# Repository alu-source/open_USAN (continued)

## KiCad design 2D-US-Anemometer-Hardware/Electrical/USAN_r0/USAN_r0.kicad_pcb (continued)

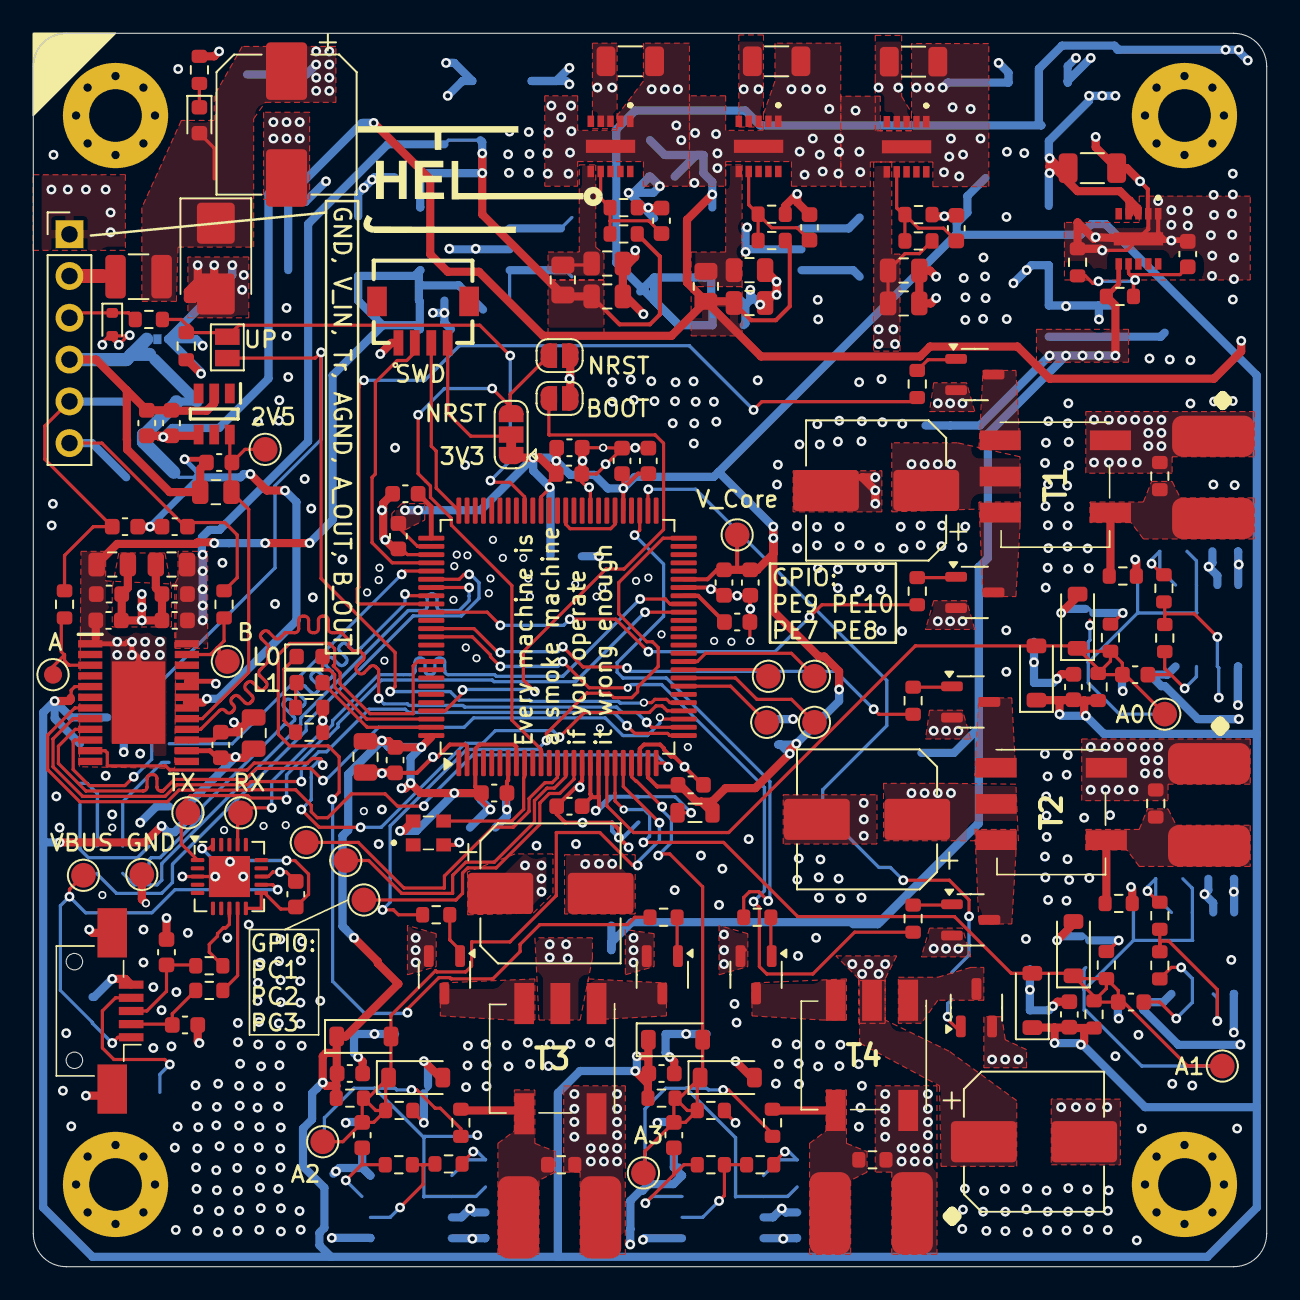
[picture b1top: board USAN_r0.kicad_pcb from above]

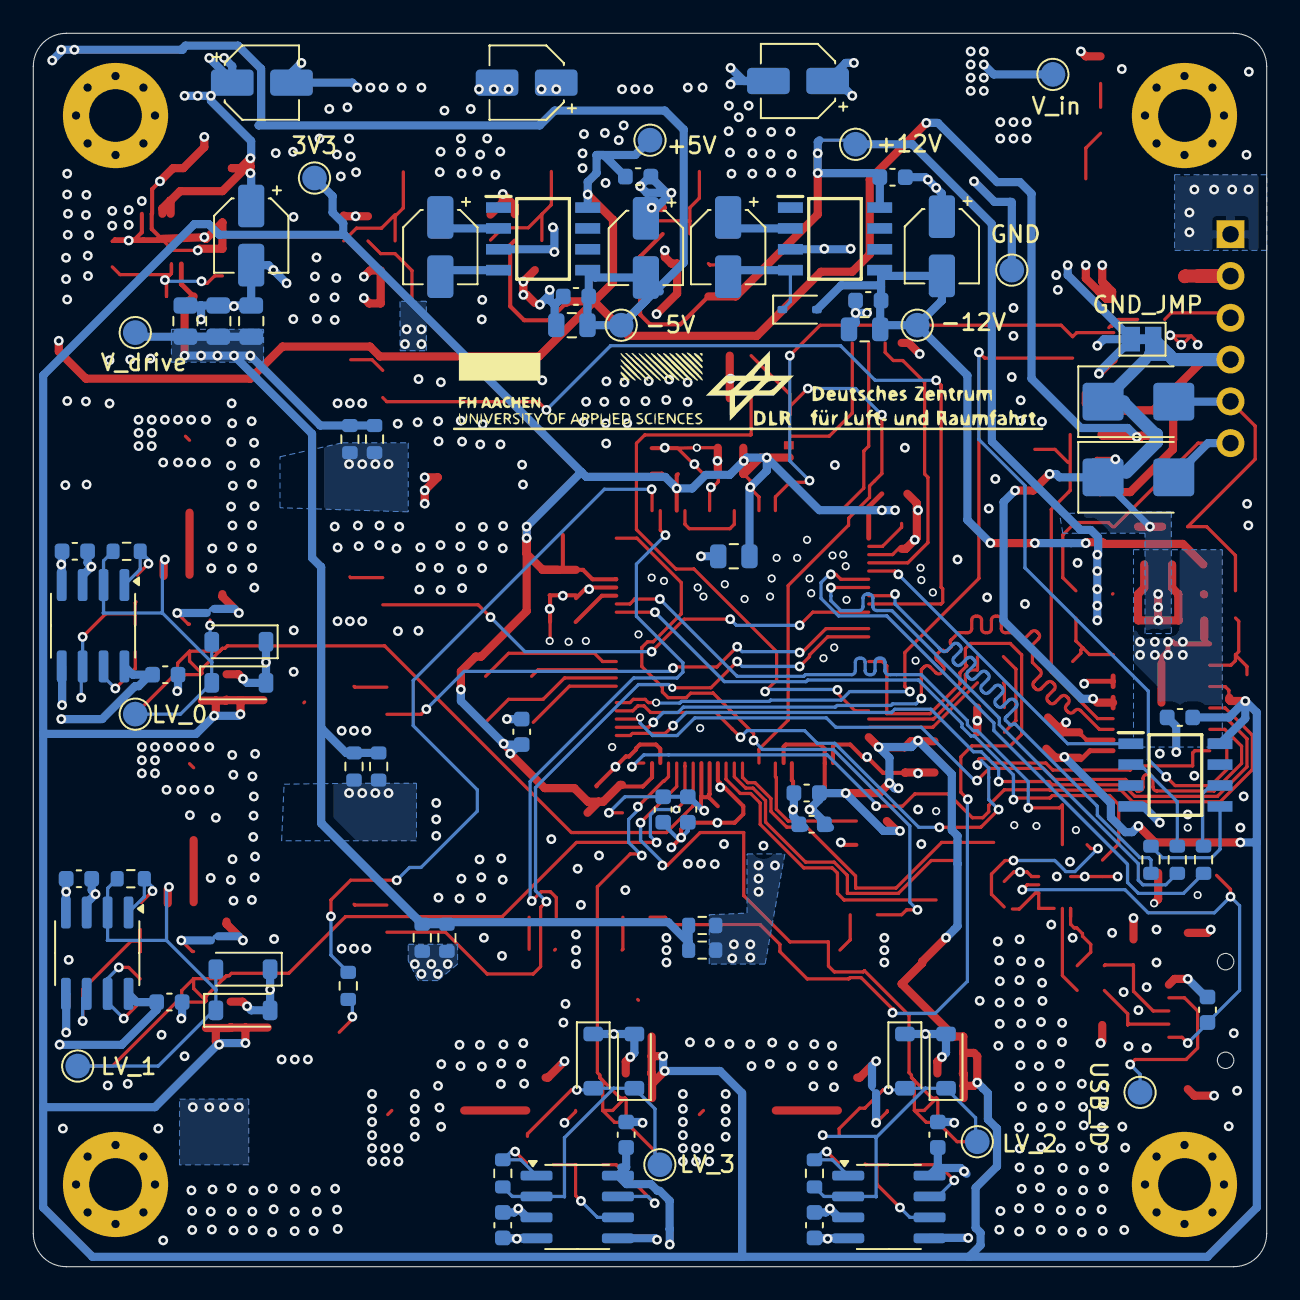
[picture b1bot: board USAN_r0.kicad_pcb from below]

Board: 4 copper layers, 75.0 x 75.0 mm, 259 parts (81 on the bottom side), 123 nets.

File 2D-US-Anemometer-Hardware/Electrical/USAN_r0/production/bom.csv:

Designator,Footprint,Quantity,Value,LCSC Part #
"C1, C28, C6, C67",0805,4,22u,
"C10, C11, C12, C13, C2, C86, C89, C9",CP_Elec_4x5.4,8,"10u, 35V",
C14,CP_Elec_8x10,1,"220uF, 35V",
"C15, C27, C33, C38, C39, C43, C46, C47, C49, C50, C53, C55, C56, C57, C59, C60, C61, C63, C64, C65, C75, C76, C77, C78",0603,24,1u,
"C16, C22, C44, C45, C69, C70, C85",0805,7,4u7,
"C17, C20",0805,2,"4u7, 25V",
"C18, C19, C83, C84",0603,4,"100n, 25V",
"C21, C23, C26, C34, C35, C36, C37, C40, C41, C42, C51, C52, C79, C80, C81",0603,15,100n,
"C29, C30",0603,2,47p,
"C31, C32",0603,2,2u2,
"C4, C82, C88, C92",1206,4,C3216X5R1H106K160AB,
"C48, C54, C58, C62",CP_Elec_8x6.2,4,EEEFK1C221P,
C66,0805,1,DNP (22u),
"C7, C91",0805,2,"10u, 25V",
"C71, C72, C73, C74",0603,4,1u ,
C87,0805,1,10u,
D1,D_SMB,1,    SMBJ24A,
"D10, D11, D12, D13, D14, D15, D16, D17, D18, D19, D4, D5, D6, D7, D8, D9",D_SOD-123,16,BAV20W,
"D2, D20, D3",0603,3,LED Blue,
D21,D_SOD-523,1,ESD5Z5.0T1G,
"D22, D23",D_SMB,2,SMBJ10CA-E3/52,
D25,D_SOD-323,1,BAT54WS-7-F,
F1,1210,1,SMD1210B020TF,
FB1,0805,1,MLZ2012N100LT000 ,
"IC1, IC2",SOIC127P600X175-8N,2,ICL7660ACBAZA,
IC3,SOP65P640X120-25N,1,AD5732AREZ,
IC4,SOT95P280X145-6N,1,REF3425TIDBVR,
IC5,SOIC127P600X175-8N,1,DNP (IS66WVS4M8BLL-104NLI-TR),
"ID1, T_-12V1, T_-5V1, T_12V1, T_24V1, T_3V3, T_5V1, T_Analog1, T_Analog2, T_Analog3, T_Analog4, T_DAC_A1, T_DAC_B1, T_GND1, T_GND2, T_GND3, T_GND4, T_GND5, T_PC1, T_PC2, T_PC3, T_PE10, T_PE7, T_PE8, T_PE9, T_RX1, T_TR_A1, T_TX1, T_VBUS1, T_V_ADJ1, T_V_MCU1, T_V_ref1",TestPoint_Pad_D1.5mm,32,TestPoint,
IN1,PinHeader_1x06_P2.54mm_Vertical,1,DNP (Conn_01x06),
J1,USB_Mini-B_AdamTech_MUSB-B5-S-VT-TSMT-1_SMD_Vertical,1,MUSB-B5-S-VT-TSMT-T/R,
J3,501331-0407,1,501331-0407,
"Q1, Q10, Q11, Q2, Q4, Q5, Q7, Q8",SOT-23-3,8,SI2300DS,
"R1, R19, R20, R29, R30, R43, R44, R57, R58",0603,9,33k,
"R10, R32, R46, R60",0603,4,10k,
"R11, R33, R47, R61",0603,4,1.5k,
"R12, R14, R16, R22, R24, R36, R50, R66",0603,8,47k,
R13,0603,1,20.5k,
"R15, R23, R37, R51",0603,4,6.2k,
"R17, R27, R41, R55",0603,4,100k,
R18,0603,1,11.5k,
R2,0603,1,4k7,
"R21, R26, R35, R4, R40, R49, R54, R9",0603,8,330R,
"R25, R3, R39, R53, R75, R76, R77, R78",0603,8,120R,
R28,0603,1,4.3k,
"R31, R34",0805,2,0R,
"R5, R6",0603,2,27R,
"R68, R69, R7, R70, R71, R8",0603,6,1k,
"R72, R73, R74",0603,3,DNP (27),
"T1, T2, T3, T4",B78416A2232A003,4,B78416A2232A003,
U1,QFN-20-1EP_4x4mm_P0.5mm_EP2.5x2.5mm,1,FT231XQ,
U2,LQFP-100_14x14mm_P0.5mm,1,STM32F469VGTx,
"U3, U4, U5, U6",SOIC-8_3.9x4.9mm_P1.27mm,4,TS912ID,
"V_ADJ1, V_ADJ2, V_ADJ3, V_ADJ4",LMZM23600SILT,4,LMZM23600SILR,
Y1,ECS2520MV250BNTR,1,ECS-2520MV-160-CN-TR,

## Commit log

2025-09-25 add plots
2025-09-25 Firmware
2025-09-25 Add CAD and KiCAD
2025-09-26 add CAD parts
2026-01-12 firmware fix
2026-01-12 miniscule
